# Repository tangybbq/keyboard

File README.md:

# David Brown (d3zd3z) keyboard designs

This repo captures the design files associated with my custom
keyboards.

These keyboards are primarily focused on Steno input, mainly using
[Plover](https://www.openstenoproject.org/plover/). In the spirit of
open steno, I have made these designs open. Anyone is free to make
designs based on these keyboards, for non-commercial purposes.  I am
releasing the designs under the [CC BY-NC
3.0](https://creativecommons.org/licenses/by-nc/3.0/) license.
Specifically, this means if you wish to sell a product based on the
design, you should talk to me.

## The "Jolt" keyboard

At this point, I've decided to give the keyboard a real name, hence "jolt".  The jolt 1 is still in
Eagle, and I may migrate the files here.

But, I have added the "jolt2".  The jolt2 is an experiment beyond just a traditional corne-like
keyboard, and something fully in 3-space, like the dactyl.  There are individual base plates for
left and right, and then small strips of 3 keys for each column.  The base PCB has 4 pairs of pin
headers to support these individual 3-key columns.  This will allow me to experiment with elevation
as well as just the X and Y position of each key.  I still want each column to be at the same
elevation, because I rely heavily on pressing keys together (both for my qwerty layout, and for
steno).

At this point, there are 4 PCBs here:

- [jolt2-left](jolt2/jolt2-left/): The layout of the left
  side using a directly assembled rp2040
- [jolt2-tiny2040-left](jolt2/jolt2-tiny2040-left/): The same left side pcb, but built around the [Pimoroni
  Tiny 2040](https://shop.pimoroni.com/products/tiny-2040?variant=39560012234835).  Note that only
  the left side needs the 8MB version (to hold the steno dictionary), but I just ordered all the
  same, and use the 8MB version on each side.
- [jolt2-tiny2040-right](jolt2/jolt2-tiny2040-right/): The Tiny 2040-based, made for the right side.
- [jolt2-verts](jolt2/jolt2-verts/): These are the small 3-key support boards.  It will take 28 of these,
  plus a left and a right to build a full keyboard.

In addition, there is also a [jolt2-pim-left](jolt2/jolt2-pim-left/), based around the [Pimoroni
PGA2350](https://shop.pimoroni.com/products/pga2350?variant=42092629229651).  There are numerous
errors in this that need to be fixed, as I messed up the reference numbers for the headers to the
key-boards.

## The "bletest2"

This isn't really a keyboard, but my experiments putting an nRF5340 module on a board.  This is work
in progress, and has numerous things I've discovered wrong with it.  I will work to improve it over
time:

- The power supply was suppose to auto switch between USB power and battery power.  However, I
  accidentally chose a boost converter instead of a boost/buck converter, and if USB is connected,
  all it does is fry everything on the board.  You can either leave out D1, or install a chain of
  diodes in its place (I used 5) to drop the voltage enough to make VBUS less than the 3.3.
  Auto-switching will probably end up preferring the battery, though, so I just recommend removing
  D1 entirely, and powering the board off of the batteries.
- The RGB LEDs don't work.  I'm not quite sure what is wrong, as I see no signal on the DIN pin.  I
  maybe have issues, given the difficult of properly soldering down the BLE module.
- The LEDs probably need a 5V supply, which isn't readily available.  Realistically, if I build a
  battery power device, I'll likely just use an analog RGB component, and use 3 gpios with PWM.

The intent was to be able to remove the various jumpers, and use the Power Profiler Kit II to
observer power consumption.  Despite rev 2, I'm still not far enough along with this to be able to
do that meaningfully.

## The "shield-kb1"

This is an Arduino-style shield, designed to plug into the nRF5340 DK.  It provides non-working
LEDs, a 2x2 keyboard matrix, and inter-board headers for left and right that should allow it to talk
to the jolt or proto3 designs.

## The "proto3"

This is basically the same design as the proto2, but with a third row.
The qmk supports an easier qwerty mode, but still with a modified
homerow modifier support (I use the lower row as it has slightly fewer
rollover conflicts).

The BOM is the same as the proto2, but it will need 42 diodes.

## The "proto2"

For lack of a better name, this first design is called the "proto2".

There was an earlier prototype, that was handwired, and rather
fragile.  This is the first version I would consider to be a usable
keyboard.  In the above pictures, the left half has the MCU (Pro Micro
RP2040) soldered directly to a header, soldered to the PCB, and the
right one uses a socket.

To build this, in addition to the PCBs, you will need

- 2 [Pro Micro RP2040](https://www.sparkfun.com/products/18288)
  boards.  At the time of my build, these are running about $11, and
  seem readily available.
- 30 Kailh Choc switches.  I sourced mine from
  [Mkultra](https://mkultra.click/choc-switches).  I recommend the
  "pink" version, which has 20gf springs, and I find work well.
- 30 keycaps for these switches.  I used the [MBK Factory
  Colors](https://mkultra.click/mbk-factory-colors/) keycaps, which
  allows me to make the "primary" keys stand out a little, and just
  looks rather nice.
- 30 general purpose SOD123 diodes.  I got
  [BAV19W](https://www.digikey.com/en/products/detail/smc-diode-solutions/BAV19W/5993796),
  although almost any diode will work for this.
- 2 or 4 5-pin right angle headers.  Two are needed for the
  communication between the boards.  The others are interested if you
  want to use SWD, since the RP2040 Pro Micro inconveniently puts
  these connectors on the underside of the board.

The PCB is reversable.  The RP2040 board should be mounted in the
labeled holes, which is always the left set when viewed from the top.
The diodes are intended to be soldered to the bottom side of the
board.

I have also a case design that can be 3d printed.  The models are for
the right side. Use your slicing software to mirror about the X axis
to print the pieces for the other side.

The firmware I am using for this keyboard is in my fork of
[QMK](https://github.com/tangybbq/qmk_firmware/tree/proto2).

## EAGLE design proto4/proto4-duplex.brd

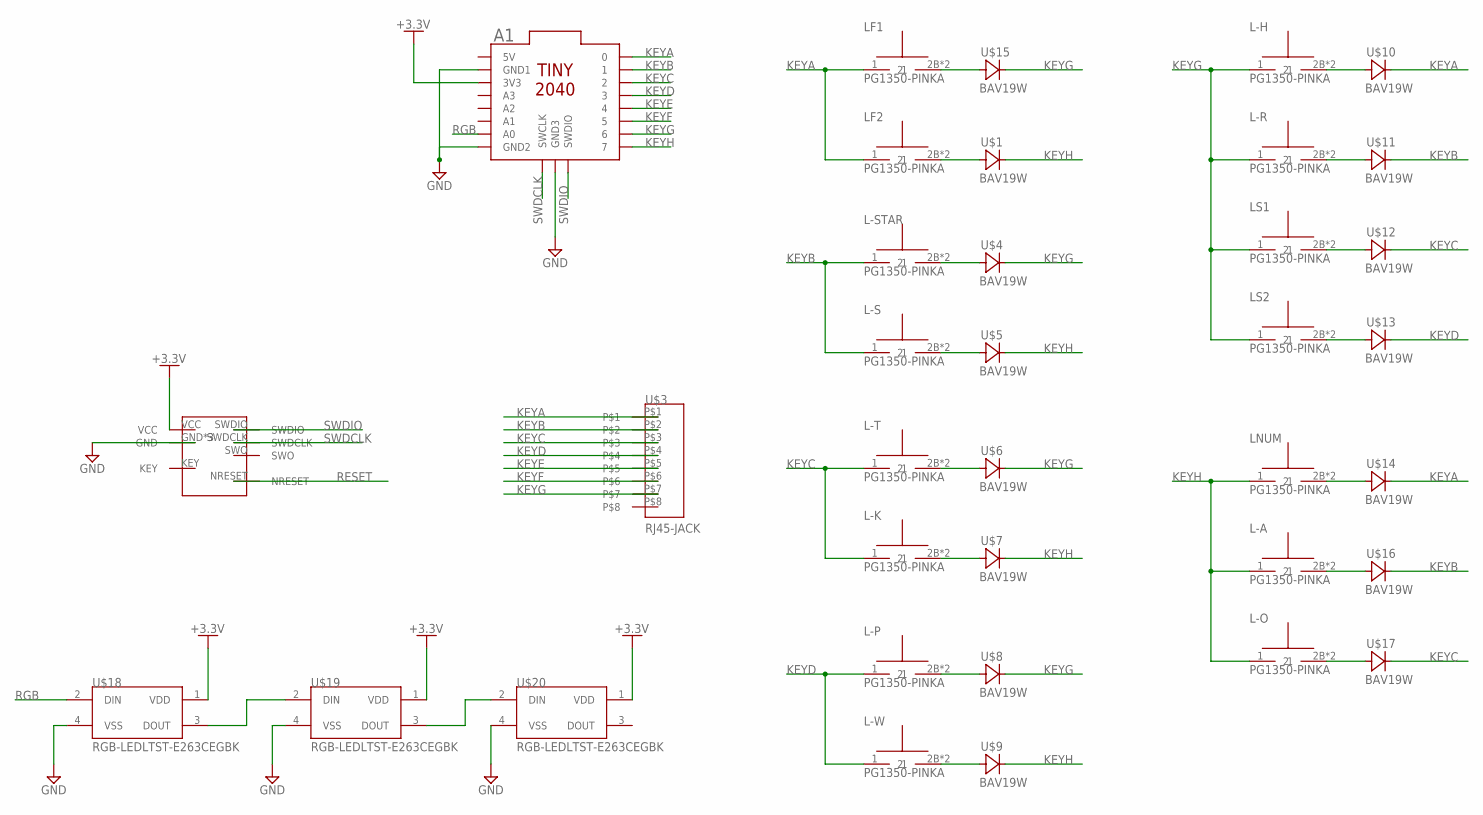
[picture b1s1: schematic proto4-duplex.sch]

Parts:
A1: TINY2040
L-A: PG1350-PINKA; PG1350
L-H: PG1350-PINKA; PG1350
L-K: PG1350-PINKA; PG1350
L-O: PG1350-PINKA; PG1350
L-P: PG1350-PINKA; PG1350
L-R: PG1350-PINKA; PG1350
L-S: PG1350-PINKA; PG1350
L-STAR: PG1350-PINKA; PG1350
L-T: PG1350-PINKA; PG1350
L-W: PG1350-PINKA; PG1350
LF1, LF2: PG1350-PINKA; PG1350
LNUM: PG1350-PINKA; PG1350
LS1, LS2: PG1350-PINKA; PG1350
U$1, U$4, U$5, U$6, U$7, U$8, U$9, U$10, U$11, U$12, U$13, U$14, U$15, U$16, U$17: BAV19W; SOD123
U$2: CORTEX-M0; CORTEX-M10
U$3: RJ45-JACK; C-BMJ-0051-RJ45
U$18, U$19, U$20: RGB-LEDLTST-E263CEGBK; DFN180X180X65-2

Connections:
+3.3V: A1.3V3, U$18.1 (VDD), U$19.1 (VDD), U$20.1 (VDD)
GND: A1.GND1, A1.GND2, A1.GND3, U$2.GND, U$2.GND2 (GND), U$2.GNDDETEC (GND), U$18.4 (VSS), U$19.4 (VSS), U$20.4 (VSS)
KEYA: A1.0, LF1.1, LF2.1, U$3.P$1, U$10.C, U$14.C
KEYB: A1.1, L-S.1, L-STAR.1, U$3.P$2, U$11.C, U$16.C
KEYC: A1.2, L-K.1, L-T.1, U$3.P$3, U$12.C, U$17.C
KEYD: A1.3, L-P.1, L-W.1, U$3.P$4, U$13.C
KEYE: A1.4, U$3.P$5
KEYF: A1.5, U$3.P$6
KEYG: A1.6, L-H.1, L-R.1, LS1.1, LS2.1, U$3.P$7, U$4.C, U$6.C, U$8.C, U$15.C
KEYH: A1.7, L-A.1, L-O.1, LNUM.1, U$1.C, U$5.C, U$7.C, U$9.C
unnamed: LF1.2B (2), LF1.2T (2), U$15.A
unnamed: LF2.2B (2), LF2.2T (2), U$1.A
unnamed: L-STAR.2B (2), L-STAR.2T (2), U$4.A
unnamed: L-S.2B (2), L-S.2T (2), U$5.A
unnamed: L-T.2B (2), L-T.2T (2), U$6.A
unnamed: L-K.2B (2), L-K.2T (2), U$7.A
unnamed: L-P.2B (2), L-P.2T (2), U$8.A
unnamed: L-W.2B (2), L-W.2T (2), U$9.A
unnamed: L-H.2B (2), L-H.2T (2), U$10.A
unnamed: L-R.2B (2), L-R.2T (2), U$11.A
unnamed: LS1.2B (2), LS1.2T (2), U$12.A
unnamed: LS2.2B (2), LS2.2T (2), U$13.A
unnamed: LNUM.2B (2), LNUM.2T (2), U$14.A
unnamed: L-A.2B (2), L-A.2T (2), U$16.A
unnamed: L-O.2B (2), L-O.2T (2), U$17.A
unnamed: U$18.3 (DOUT), U$19.2 (DIN)
unnamed: U$19.3 (DOUT), U$20.2 (DIN)
RESET: U$2.NRESET
RGB: A1.A0, U$18.2 (DIN)
SWDCLK: A1.SWCLK, U$2.SWDCLK
SWDIO: A1.SWDIO, U$2.SWDIO

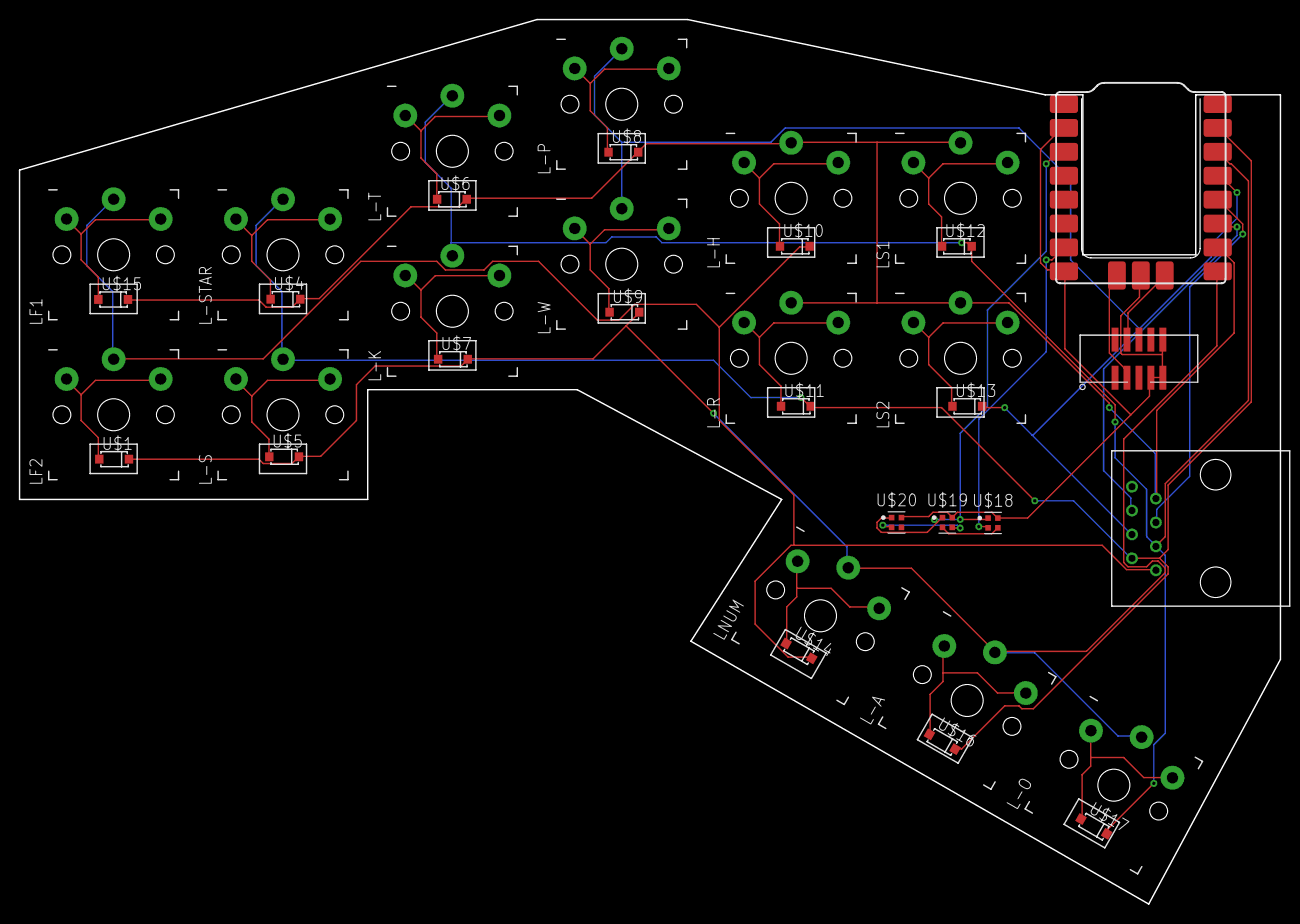
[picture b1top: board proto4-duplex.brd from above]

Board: 2 copper layers, 134.0 x 94.0 mm, 36 parts (0 on the bottom side), 30 nets.

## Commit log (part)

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2022-10-30 Create initial proto2 with images
2022-10-30 Fix images to show inline
2022-10-30 Include firmware reference.
2022-10-30 Add design files for the proto2
2022-11-15 Update README for the proto3
2022-11-15 Add design files for proto3
2024-02-23 Add initial qwerty diagram
2024-02-23 Add qwerty diagram
    This describes my layout for the 3-row keyboard qwerty mode. There are
    lots of combos, which works well, as the keys are designed to be pressed
    this way. There are also three layers for numbers, navigation, and
    function keys.
    The number layer also adds keys for hex, with 'e' in a weird place,
    because the regular 'e' key is taken by a '3'.
2024-12-06 Add my footprint and symbol libraries
2024-12-06 Add bletest project
2024-12-07 Full routing done
    There are still a bunch of ERC violations.
2024-12-07 Clean up most ERC violations
    The remaining are silkscreen overlaps or clipping issues.
2024-12-16 jolt2: Add Initial WIP
    The jolt is a "3D" staggered keyboard. There are 3 PCB designs here:
    - jolt2-verts: These are the 1x3 individual key segments. Each holds
    3 keys and is a vertical column.
    - jolt2-left: The base of the left side of the keyboard. This is the
    side intended to be plugged into the host.
    - jolt2-right (not yet made): The right side base.
2024-12-16 shield-kb1: A keyboard prototype shield for the nRF DK boards
    This initial one has 4 keys, connectors for compatibility with left and
    right, and some LEDs.
2024-12-16 Cleanup the Cortex-M Debug footprint
    Try to make a silkscreen for it that shows the full connector, with a
    clear pin 1 indicator, that also doesn't overlap any pads.
2024-12-16 Commit some missing footprints
    The RP2040 comes from their reference schematic.
    The AP211-SO8 and QBLP600-RGB5 I've drawn from the datasheets.
2024-12-16 jolt2: Prepare rev A
    This is Rev A, being sent for production.
2024-12-16 Rev A of bletest
    Finish cleanup, and remove last remaining violations.
    There are a handful of silkscreen overlaps with explicit exclusions.
2024-12-16 shield-kb1: rev-b updates: LEDs
    In addition to actually hooking up the switches, add a PWM RGB LED. It
    is hard to find these that will work with 3.2V, hopefully this one will.
    It is fairly small, and I've come up with some resistors for about 15mA.
    I've also added a jumper to allow the SK6812 to be powered either from
    3.3V or 5V, which should help figring out issues with that.
2024-12-16 bletest-2: Minor layer visibility change
2024-12-16 jolt2-tiny204-left: Cleanup and route
    Fix the designators for all of the pin headers. This was mostly done
    manually, naming them consistently for each component.
    Perform manual routing.
    This should be ready for REV A.
2024-12-16 Remove some stray committed files
2024-12-16 jolt2: add pim-left board
    Copy the current left board, to jolt2-pim-left, which will be
    re-designed using the PIM722, the Pimoroni 25.4mm x 25.4mm PGA board.
2024-12-16 Create jolt2-tiny2040-left
    The jump references are messed up, and I'm going to edit the text file
    directly to fix them.
2024-12-16 jolt2-pim-left: Finalize routing
2024-12-16 bletest-2: Remove xls bom
2024-12-16 bletest-2: update xls bom
    This file is not actually useful, as the html bom from the KiCad plugin
    is much more useful.
2024-12-16 jolt-tiny2040-right: Create and build rev A
    Create the right side, copying the left, and flipping everything. Route
    the result, ready for Rev A production.
2024-12-16 jolt2-pim-left: Add uart terminating resistors
    Place 27 ohm series resisters on the inter-board uart lines.
2024-12-16 jolt2-left: Add inter-board termination
    Add 27 ohm resisters for termination on the inter-board protocol.
2024-12-16 README: Update with the new KiCad designs
2024-12-16 Rename jolt-tiny2040-right to jolt2-tiny2040-right
    Fix the name to align with the rest of the PCBs.
2024-12-17 Copy jolt2-tiny2040-left to jolt2-pm2350-left
    Start on the 2350 PCB by copying the tiny2040.
2024-12-17 jolt2: Update pm2350 left footprint
    Build the footprint, updating it for the left side of the keyboard
2024-12-24 jolt2-tiny2040-right: Update PCB from schematic
    Schematic was missing swapping TX and RX.
2025-01-04 Various PCB updates
    This is before fixing the footprint for the WS2812. Turns out there is a
    ws2812 MINI, and a MINI-HS, and they have very different footprints.
2025-01-04 jolt2-left: Fix symbol and footprint for ws2812
    The ws2812 has both a MINI and a MINI-HS footprint, and they have rather
    different footprints. Update the symbol and draw a footprint for the
    proper one we have purchased.
2025-01-04 Add assembly instructions for the jolt2
    Write up some basic instructions with photos.
2025-01-14 jolt2-left: Add some calibration circles
    Add some calibration circles to a user layer that can be included in a
    CAD export and should help determining the position of the keys.
2025-01-22 jolt3: First pass
    This defines a mezzanine board, with connector, and separate left and
    right sides.
    This design doesn't work with the right side, as the connector
    interferes with the RJ-45, so I have to position that differently.
2025-01-22 Jolt 3: Rev A for 3 boards
    Send Rev A out for jolt3-left, jolt3-right, and j3-mez-2040.
2025-01-24 Update the Jolt3 Readme
2025-01-24 Jolt3 RevA updated ibom files
    Update the jolt3 ibom files for the Rev A sent to manufacturing.
2025-01-24 Jolt 3: Add notes about the Tag-Connect
    The jolt3 moves away from the Cortex-M debug header to the Tag-Connect,
    saving money and assembly work per board, at the cost of a single $45
    cable.
2026-04-19 Update for latest KiCad
    This seems to have done a rewrite of uuids within the files.
